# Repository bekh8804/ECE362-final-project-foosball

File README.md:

# ECE362-final-project-foosball
Patchy Was here
Gideon Was here

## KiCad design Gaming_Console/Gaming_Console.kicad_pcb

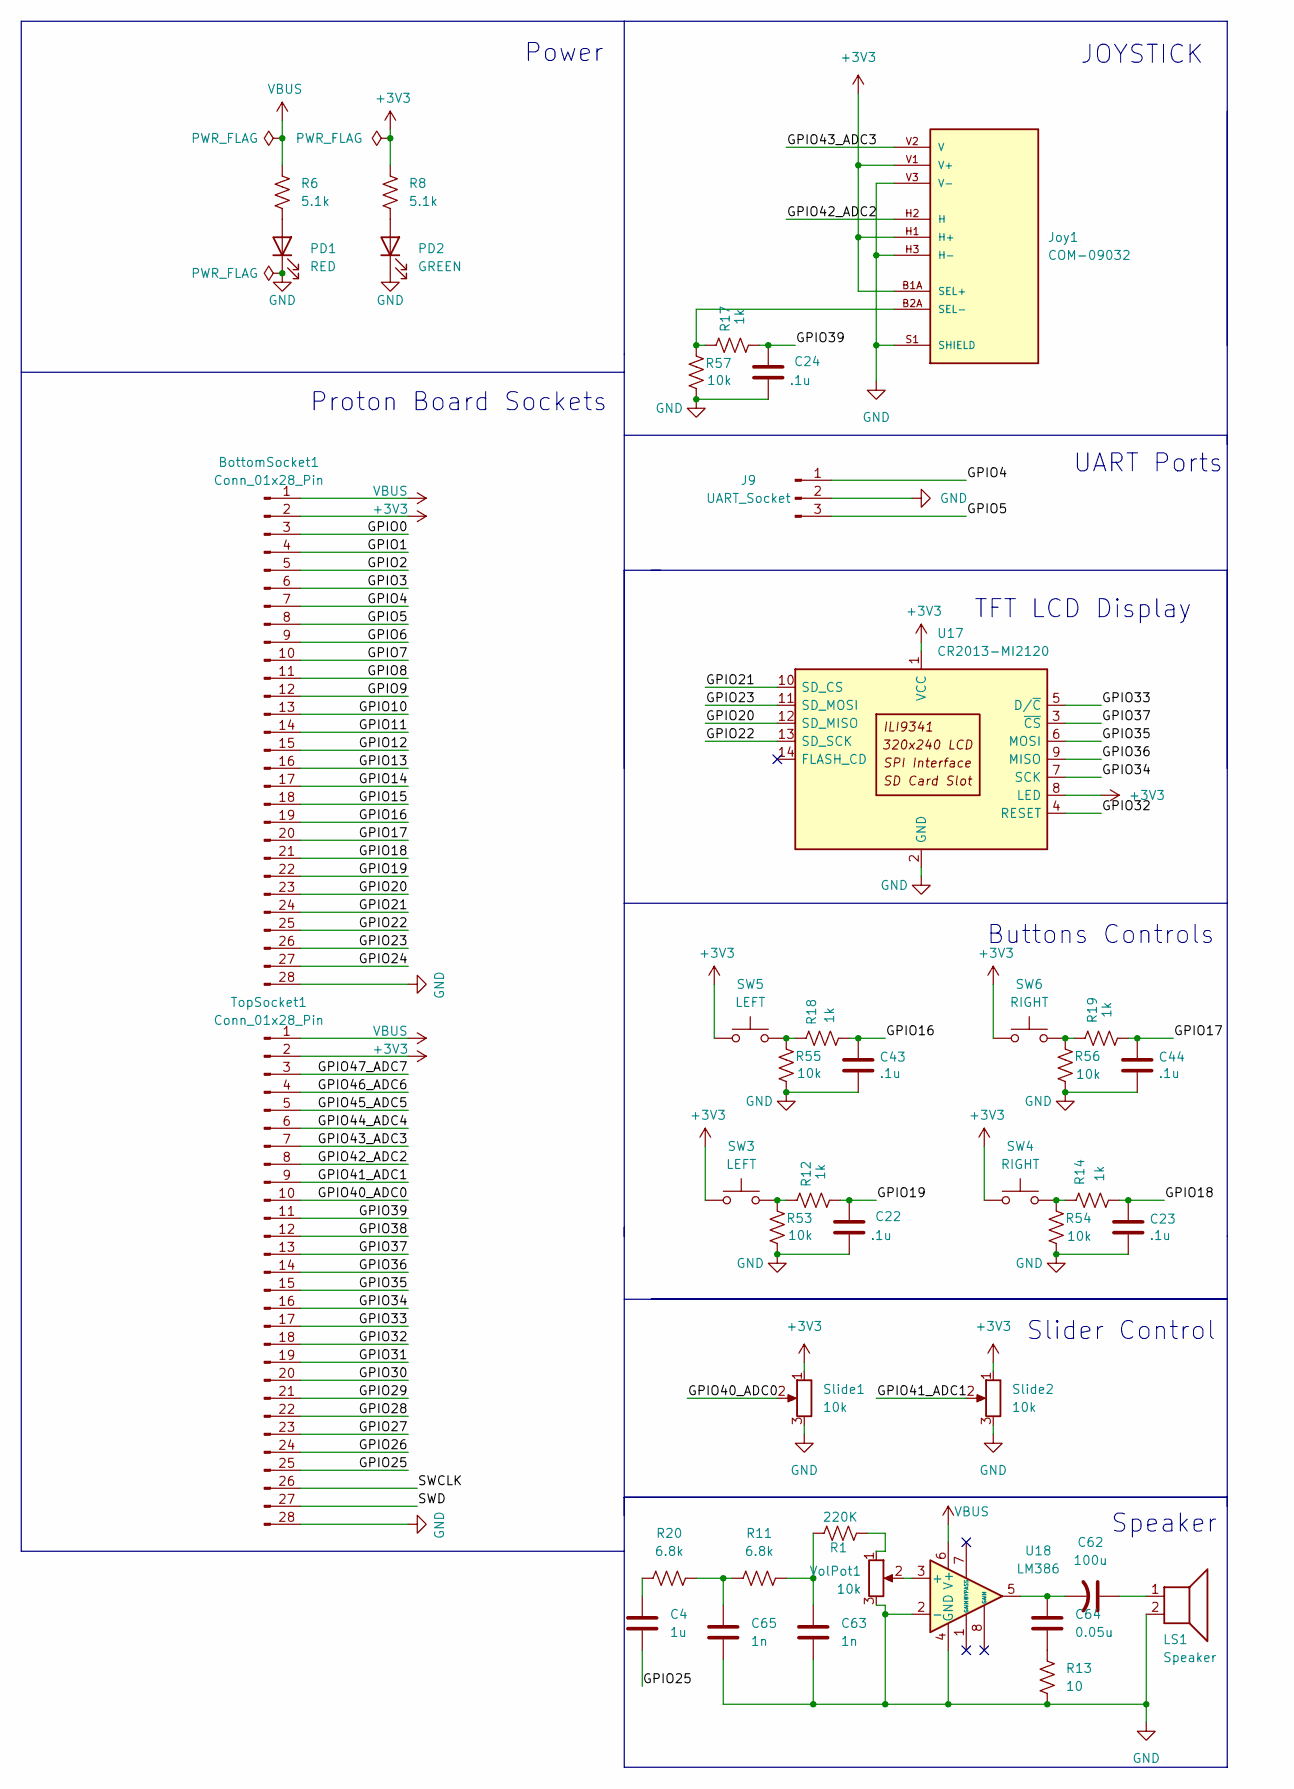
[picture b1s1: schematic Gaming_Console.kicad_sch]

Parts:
BottomSocket1: Conn_01x28_Pin; PinSocket_1x28_P2.54mm_Vertical
C4: 1u; C_0805_2012Metric
C22, C23, C24, C43, C44: .1u; C_0805_2012Metric
C62: 100u; C_0805_2012Metric
C63, C65: 1n; C_0805_2012Metric
C64: 0.05u; C_0805_2012Metric
J9: UART_Socket; JST_PH_S3B-PH-K_1x03_P2.00mm_Horizontal; MPN PRPC003SACN-RC
Joy1: COM-09032; XDCR_COM-09032; MPN COM-09032
LS1: Speaker; Speaker_CUI_CMR-1206S-67
PD1: RED; LED_0805_2012Metric; MPN LS R976-NR-1-0-20-R18
PD2: GREEN; LED_0805_2012Metric; MPN LG R971-KN-1-0-20-R18
R1: 220K; R_0805_2012Metric
R6, R8: 5.1k; R_0805_2012Metric; MPN RK73H1ETTP5101F
R11, R20: 6.8k; R_0805_2012Metric
R12, R14, R17, R18, R19: 1k; R_0805_2012Metric; MPN RC0402JR-071KL
R13: 10; R_0805_2012Metric
R53, R54, R55, R56, R57: 10k; R_0805_2012Metric
SW3, SW5: LEFT; SW_SPST_PTS647_Sx38; MPN PTS647SM38SMTR2 LFS
SW4, SW6: RIGHT; SW_SPST_PTS647_Sx38; MPN PTS647SM38SMTR2 LFS
Slide1, Slide2: 10k; Potentiometer_Bourns_PTA2043_Single_Slide
TopSocket1: Conn_01x28_Pin; PinSocket_1x28_P2.54mm_Vertical
U17: CR2013-MI2120
U18: LM386; DIP-8_W7.62mm
VolPot1: 10k; Potentiometer_Alps_RK09K_Single_Vertical

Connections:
+3V3: BottomSocket1.2, Joy1.B1A (SEL+), Joy1.H1 (H+), Joy1.V1 (V+), R8.1, SW3.1, SW4.1, SW5.1, SW6.1, Slide1.1, Slide2.1, TopSocket1.2, U17.1 (VCC), U17.8 (LED)
/GPIO0: BottomSocket1.3
/GPIO1: BottomSocket1.4
/GPIO2: BottomSocket1.5
/GPIO3: BottomSocket1.6
/GPIO4: BottomSocket1.7, J9.1
/GPIO5: BottomSocket1.8, J9.3
/GPIO6: BottomSocket1.9
/GPIO7: BottomSocket1.10
/GPIO8: BottomSocket1.11
/GPIO9: BottomSocket1.12
/GPIO10: BottomSocket1.13
/GPIO11: BottomSocket1.14
/GPIO12: BottomSocket1.15
/GPIO13: BottomSocket1.16
/GPIO14: BottomSocket1.17
/GPIO15: BottomSocket1.18
/GPIO16: BottomSocket1.19, C43.1, R18.2
/GPIO17: BottomSocket1.20, C44.1, R19.2
/GPIO18: BottomSocket1.21, C23.1, R14.2
/GPIO19: BottomSocket1.22, C22.1, R12.2
/GPIO20: BottomSocket1.23, U17.12 (SD_MISO)
/GPIO21: BottomSocket1.24, U17.10 (SD_CS)
/GPIO22: BottomSocket1.25, U17.13 (SD_SCK)
/GPIO23: BottomSocket1.26, U17.11 (SD_MOSI)
/GPIO24: BottomSocket1.27
/GPIO25: C4.2, TopSocket1.25
/GPIO26: TopSocket1.24
/GPIO27: TopSocket1.23
/GPIO28: TopSocket1.22
/GPIO29: TopSocket1.21
/GPIO30: TopSocket1.20
/GPIO31: TopSocket1.19
/GPIO32: TopSocket1.18, U17.4 (RESET)
/GPIO33: TopSocket1.17, U17.5 (D/~C)
/GPIO34: TopSocket1.16, U17.7 (SCK)
/GPIO35: TopSocket1.15, U17.6 (MOSI)
/GPIO36: TopSocket1.14, U17.9 (MISO)
/GPIO37: TopSocket1.13, U17.3 (~CS)
/GPIO38: TopSocket1.12
/GPIO39: C24.1, R17.2, TopSocket1.11
/GPIO40_ADC0: Slide1.2, TopSocket1.10
/GPIO41_ADC1: Slide2.2, TopSocket1.9
/GPIO42_ADC2: Joy1.H2 (H), TopSocket1.8
/GPIO43_ADC3: Joy1.V2 (V), TopSocket1.7
/GPIO44_ADC4: TopSocket1.6
/GPIO45_ADC5: TopSocket1.5
/GPIO46_ADC6: TopSocket1.4
/GPIO47_ADC7: TopSocket1.3
/SWCLK: TopSocket1.26
/SWD: TopSocket1.27
GND: BottomSocket1.28, C22.2, C23.2, C24.2, C43.2, C44.2, C63.2, C65.2, J9.2, Joy1.H3 (H-), Joy1.S1 (SHIELD), Joy1.S2 (SHIELD), Joy1.S3 (SHIELD), Joy1.S4 (SHIELD), Joy1.V3 (V-), LS1.2, PD1.1 (K), PD2.1 (K), R13.2, R53.1, R54.1, R55.1, R56.1, R57.1, Slide1.3, Slide2.3, TopSocket1.28, U17.2 (GND), U18.2 (-), U18.4 (GND), VolPot1.3
unnamed: C4.1, R20.2
unnamed: C62.1, LS1.1
unnamed: C62.2, C64.1, U18.5
unnamed: C63.1, R1.1, R11.1
unnamed: C64.2, R13.1
unnamed: C65.1, R11.2, R20.1
unnamed: Joy1.B2A (SEL-), R17.1, R57.2
unnamed: PD1.2 (A), R6.2
unnamed: PD2.2 (A), R8.2
unnamed: R1.2, VolPot1.1
unnamed: R12.1, R53.2, SW3.2
unnamed: R14.1, R54.2, SW4.2
unnamed: R18.1, R55.2, SW5.2
unnamed: R19.1, R56.2, SW6.2
unnamed: U18.3 (+), VolPot1.2
VBUS: BottomSocket1.1, R6.1, TopSocket1.1, U18.6 (V+)

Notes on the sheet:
TFT LCD Display
Power
Slider Control
UART Ports
JOYSTICK
Buttons Controls
Proton Board Sockets
Speaker

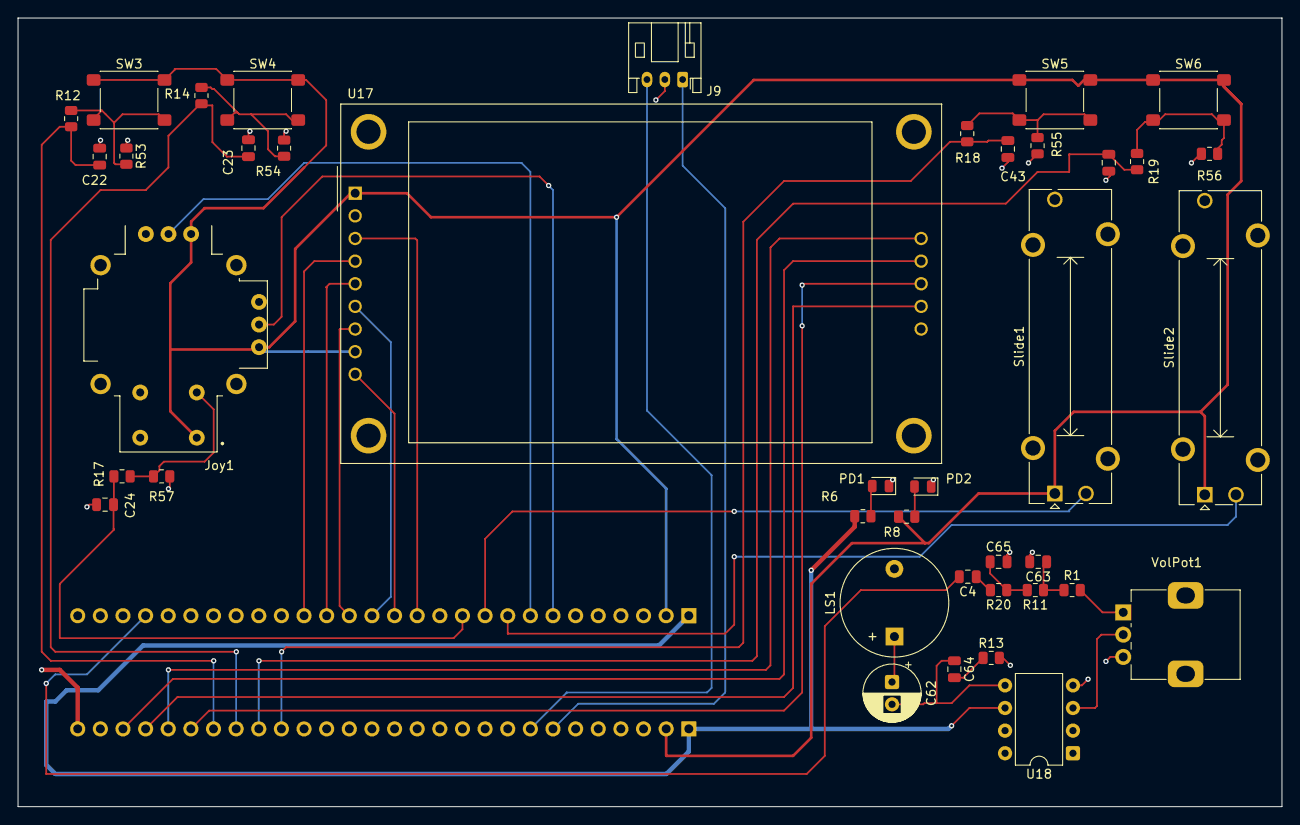
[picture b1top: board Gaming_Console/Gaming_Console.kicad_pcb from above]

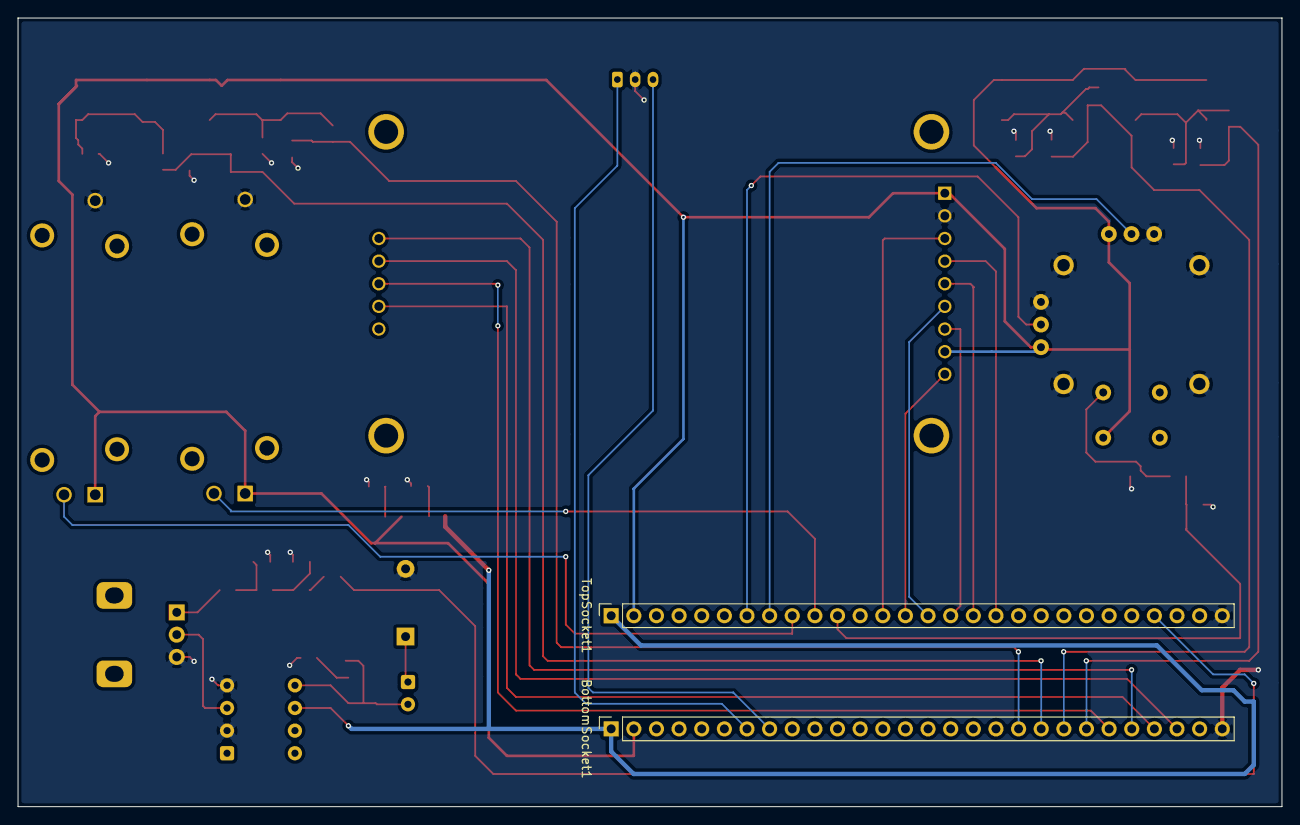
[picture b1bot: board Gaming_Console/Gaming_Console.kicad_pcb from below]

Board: 2 copper layers, 141.8 x 88.5 mm, 42 parts (2 on the bottom side), 40 nets.

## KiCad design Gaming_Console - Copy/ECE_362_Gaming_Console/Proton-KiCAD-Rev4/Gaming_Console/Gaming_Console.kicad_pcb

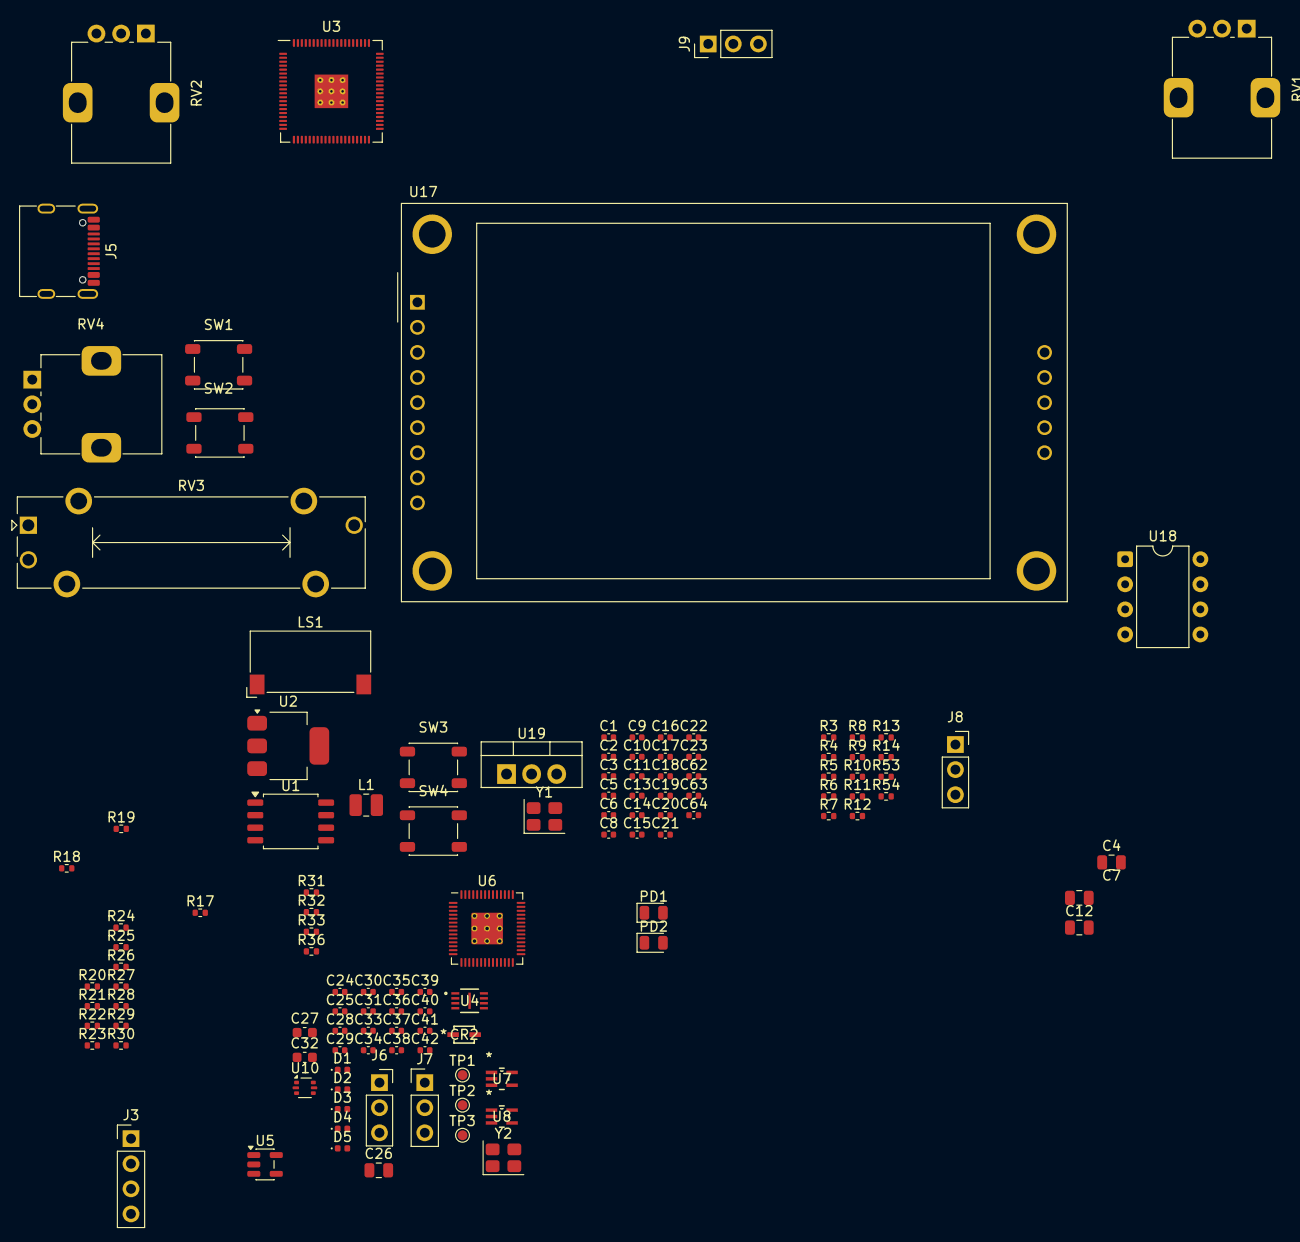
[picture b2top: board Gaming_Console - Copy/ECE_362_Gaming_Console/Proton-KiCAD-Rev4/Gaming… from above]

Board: 2 copper layers, 118 parts (0 on the bottom side), 96 nets, no tracks yet.

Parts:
C1, C2, C24, C25: 15p; C_0402_1005Metric
C3, C8, C11, C13, C14, C15, C16, C17, C18, C19, C20, C21, C28, C29, C30, C33, C35, C36, C37, C38, C39, C40, C41, C42: 100n; C_0402_1005Metric
C4, C7, C12, C26: 10u; C_0805_2012Metric
C5, C6, C9, C10: 4.7u; C_0402_1005Metric
C22, C23: DNF; C_0402_1005Metric
C27, C32: 10u; C_0603_1608Metric
C31, C34: 1u; C_0402_1005Metric
C62: 100u; C_0402_1005Metric
C63: 1n; C_0402_1005Metric
C64: 0.05u; C_0402_1005Metric
CR2: BAT60JFILM; CR_60JFILM_STM
D1: RED; D_0402_1005Metric
D2, D4: GREEN; D_0402_1005Metric
D3, D5: YELLOW; D_0402_1005Metric
J3: Conn_01x04_Pin; PinHeader_1x04_P2.54mm_Vertical
J5: USB_C_Receptacle_USB2.0_14P; USB_C_Receptacle_G-Switch_GT-USB-7010ASV
J6, J8: Conn_01x03_Socket; PinSocket_1x03_P2.54mm_Vertical
J7: UART-PINS; PinHeader_1x03_P2.54mm_Vertical
J9: UART_Socket; PinHeader_1x03_P2.54mm_Vertical
L1: 3.3u; L_1008_2520Metric
LS1: Speaker; Speaker_CUI_CMR-1206S-67
PD1: RED; LED_0805_2012Metric
PD2: GREEN; LED_0805_2012Metric
R3, R4, R7, R12, R14, R17, R20, R36: 1k; R_0402_1005Metric
R5: 33; R_0402_1005Metric
R6, R8, R18, R19: 5.1k; R_0402_1005Metric
R9, R10, R21, R22: 27; R_0402_1005Metric
R11: 10k; R_0402_1005Metric
R13: 10; R_0402_1005Metric
R23, R31, R33: 470; R_0402_1005Metric
R24, R25, R26, R27, R28, R29: 100; R_0402_1005Metric
R30, R32: 2k; R_0402_1005Metric
R53, R54: DNF; R_0402_1005Metric
RV1: Pot1; Potentiometer_Alps_RK09K_Single_Vertical
RV2: Pot2; Potentiometer_Alps_RK09K_Single_Vertical
RV3: Pot3; Potentiometer_Bourns_PTA2043_Single_Slide
RV4: VolPot; Potentiometer_Alps_RK09K_Single_Vertical
SW1: BOOTSEL; SW_SPST_PTS647_Sx38
SW2: RESET; SW_SPST_PTS647_Sx38
SW3: LEFT; SW_SPST_PTS647_Sx38
SW4: RIGHT; SW_SPST_PTS647_Sx38
TP1: RESET; TestPoint_Pad_D1.0mm
TP2: SWCLK; TestPoint_Pad_D1.0mm
TP3: SWD; TestPoint_Pad_D1.0mm
U1: W25Q128JVS; SOIC-8_5.3x5.3mm_P1.27mm
U2: NCP1117-3.3_SOT223; SOT-223-3_TabPin2
U3: RP2350_80QFN; RP2350-QFN-80-1EP_10x10_P0.4mm_EP3.4x3.4mm_ThermalVias
U4: W25Q16JVUXIQ TR; USON-8_UX_2x3x0p6_WIN
U5: AP2112K-3.3; SOT-23-5
U6: RP2040; RP2040-QFN-56
U7, U8: SN74AUP1T17DCKR; DCK5
U10: USBLC6-2P6; SOT-666
U17: CR2013-MI2120
U18: LM386; DIP-8_W7.62mm
U19: LM7805_TO220; TO-220-3_Vertical
Y1, Y2: ABM8-272-T3; Crystal_SMD_3225-4Pin_3.2x2.5mm

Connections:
+1V1: C6.1, C8.1, C10.1, C11.1, L1.1, U3.10 (DVDD), U3.32 (DVDD), U3.51 (DVDD), U3.65 (VREG_FB)
+3V3: C3.1, C5.1, C12.1, C13.1, C14.1, C15.1, C16.1, C17.1, C18.1, C19.1, C20.1, C21.1, R5.1, R8.1, R12.1, R14.1, RV1.1, RV2.1, RV3.1, U1.8 (VCC), U3.5 (IOVDD), U3.15 (IOVDD), U3.24 (IOVDD), U3.29 (IOVDD), U3.41 (IOVDD), U3.50 (IOVDD), U3.59 (ADC_AVDD), U3.60 (IOVDD), U3.64 (VREG_VIN), U3.68 (USB_OTP_VDD), U3.69 (QSPI_IOVDD), U3.76 (IOVDD), U17.1 (VCC), U17.8 (LED)
+P1V1: C28.1, C30.1, C31.1, U6.23 (DVDD), U6.45 (VREG_VOUT), U6.50 (DVDD)
+P3V3: C27.1, C29.1, C32.1, C33.1, C34.1, C35.1, C36.1, C37.1, C38.1, C39.1, C40.1, C41.1, C42.1, R36.1, U4.8 (VCC), U5.5 (VOUT), U6.1 (IOVDD), U6.10 (IOVDD), U6.22 (IOVDD), U6.33 (IOVDD), U6.42 (IOVDD), U6.43 (ADC_AVDD), U6.44 (VREG_IN), U6.48 (USB_VDD), U6.49 (IOVDD), U7.5 (VCC), U8.5 (VCC)
/3.3V: C7.1, U2.2 (VO)
/DebugProbe/GPIO2: R23.1, U6.4 (GPIO2)
/DebugProbe/GPIO4: R24.1, U6.6 (GPIO4)
/DebugProbe/GPIO5: U6.7 (GPIO5), U7.4 (Y)
/DebugProbe/GPIO6: R25.1, U6.8 (GPIO6)
/DebugProbe/GPIO7: R30.1, U6.9 (GPIO7)
/DebugProbe/GPIO8: R31.1, U6.11 (GPIO8)
/DebugProbe/GPIO12: R27.1, U6.15 (GPIO12)
/DebugProbe/GPIO13: U6.16 (GPIO13), U8.4 (Y)
/DebugProbe/GPIO14: R28.1, U6.17 (GPIO14)
/DebugProbe/GPIO15: R32.1, U6.18 (GPIO15)
/DebugProbe/GPIO16: R33.1, U6.27 (GPIO16)
/DebugProbe/QSPI_SCLK: U4.6 (CLK), U6.52 (QSPI_SCLK)
/DebugProbe/QSPI_SD0: U4.5 (DI(IO0)), U6.53 (QSPI_SD0)
/DebugProbe/QSPI_SD1: U4.2 (DO(IO1)), U6.55 (QSPI_SD1)
/DebugProbe/QSPI_SD2: U4.3 (/WP(IO2)), U6.54 (QSPI_SD2)
/DebugProbe/QSPI_SD3: U4.7 (/HOLDOR/RESET(IO3)), U6.51 (QSPI_SD3)
/DebugProbe/QSPI_SS: R17.1, U4.1 (/CS), U6.56 (QSPI_SS)
/DebugProbe/RESET: R36.2, TP1.1 (1_1), U6.26 (RUN)
/DebugProbe/USB_D+: R21.1, U10.4 (I/O2)
/DebugProbe/USB_D-: R22.1, U10.6 (I/O1)
/DebugProbe/XIN: C24.1, U6.20 (XIN), Y2.1
/DebugProbe/XOUT: R20.1, U6.21 (XOUT)
/DebugProbe/~USB_BOOT: J3.1, R17.2
/FLASH_SS: R7.1, U1.1 (~CS), U3.75 (QSPI_SS)
/GPIO4: J9.1, U3.1 (GPIO4)
/GPIO5: J9.3, U3.2 (GPIO5)
/GPIO18: C23.1, R54.2, SW4.2, U3.18 (GPIO18)
/GPIO19: C22.1, R53.2, SW3.2, U3.19 (GPIO19)
/GPIO20: U3.20 (GPIO20), U17.12 (SD_MISO)
/GPIO21: U3.21 (GPIO21), U17.10 (SD_CS)
/GPIO22: U3.22 (GPIO22), U17.13 (SD_SCK)
/GPIO23: U3.23 (GPIO23), U17.11 (SD_MOSI)
/GPIO25: RV4.1, U3.26 (GPIO25)
/GPIO34: U3.43 (GPIO34), U17.7 (SCK)
/GPIO35: U3.44 (GPIO35), U17.6 (MOSI)
/GPIO36: U3.45 (GPIO36), U17.9 (MISO)
/GPIO37: U3.46 (GPIO37), U17.3 (~CS)
/GPIO40_ADC0: RV1.2, U3.49 (GPIO40_ADC0)
/GPIO41_ADC1: RV2.2, U3.52 (GPIO41_ADC1)
/GPIO42_ADC2: RV3.2, U3.53 (GPIO42_ADC2)
/QSPI_SCLK: U1.6 (CLK), U3.71 (QSPI_SCLK)
/QSPI_SD0: U1.5 (DI(IO0)), U3.72 (QSPI_SD0)
/QSPI_SD1: U1.2 (DO(IO1)), U3.74 (QSPI_SD1)
/QSPI_SD2: U1.3 (IO2), U3.73 (QSPI_SD2)
/QSPI_SD3: U1.7 (IO3), U3.70 (QSPI_SD3)
/RUN: SW2.2, U3.35 (RUN), U17.4 (RESET)
/SWCLK: J8.1, U3.33 (SWCLK)
/SWD: J8.3, U3.34 (SWD)
/VREG_AVDD: C9.1, R5.2, U3.61 (VREG_AVDD)
/VREG_LX: L1.2, U3.63 (VREG_LX)
/XIN: C1.1, U3.30 (XIN), Y1.1
/XOUT: R3.1, U3.31 (XOUT)
/~USB_BOOT: R7.2, SW1.2
GND: C1.2, C2.2, C3.2, C4.2, C5.2, C6.2, C7.2, C8.2, C9.2, C10.2, C11.2, C12.2, C13.2, C14.2, C15.2, C16.2, C17.2, C18.2, C19.2, C20.2, C21.2, C22.2, C23.2, C63.2, J8.2, J9.2, LS1.2, PD1.1 (K), PD2.1 (K), R4.2, R13.2, R53.1, R54.1, RV1.3, RV2.3, RV3.3, RV4.3, SW1.1, U1.4 (GND), U2.1 (GND), U3.62 (VREG_PGND), U3.81 (GND), U17.2 (GND), U18.2 (-), U18.4 (GND), U19.2 (GND), Y1.2, Y1.4
unnamed: C2.1, R3.2, Y1.3
unnamed: C25.1, R20.2, Y2.3
unnamed: C62.1, LS1.1
unnamed: C62.2, C64.1, U18.5
unnamed: C64.2, R13.1
unnamed: CR2.2, J5.A4 (VBUS), J5.A9 (VBUS), J5.B4 (VBUS), J5.B9 (VBUS)
unnamed: D1.2 (A), R23.2
unnamed: D2.2 (A), R30.2
unnamed: D3.2 (A), R31.2
unnamed: D4.2 (A), R32.2
unnamed: D5.2 (A), R33.2
unnamed: J5.A5 (CC1), R18.1
unnamed: J5.B5 (CC2), R19.1
unnamed: J5.A6 (D+), J5.B6 (D+), U10.3 (I/O2)
unnamed: J5.A7 (D-), J5.B7 (D-), U10.1 (I/O1)
unnamed: J7.1, R24.2
unnamed: J7.3, R25.2, R26.2
unnamed: PD1.2 (A), R6.2
unnamed: PD2.2 (A), R8.2
unnamed: R4.1, SW2.1
unnamed: R11.2, RV4.2
unnamed: R12.2, SW3.1
unnamed: R14.2, SW4.1
unnamed: R10.2, U3.66 (USB_DM)
unnamed: R9.2, U3.67 (USB_DP)
unnamed: TP2.1 (1_1), U6.24 (SWCLK)
unnamed: TP3.1 (1_1), U6.25 (SWD)
unnamed: R22.2, U6.46 (USB_DM)
unnamed: R21.2, U6.47 (USB_DP)
unnamed: R26.1, U7.2 (A)
unnamed: R29.1, U8.2 (A)
unnamed: C63.1, R11.1, U18.3 (+)
PGND: C24.2, C25.2, C26.2, C27.2, C28.2, C29.2, C30.2, C31.2, C32.2, C33.2, C34.2, C35.2, C36.2, C37.2, C38.2, C39.2, C40.2, C41.2, C42.2, D1.1 (K), D2.1 (K), D3.1 (K), D4.1 (K), D5.1 (K), J3.3, J5.A1 (GND), J5.A12 (GND), J5.B1 (GND), J5.B12 (GND), J6.2, J7.2, R18.2, R19.2, U4.4 (GND), U5.2 (GND), U6.19 (TESTEN), U6.57 (GND), U7.3 (GND), U8.3 (GND), U10.2 (GND), Y2.2, Y2.4
PSWCLK: J3.2, J6.1, R27.2
PSWD: J3.4, J6.3, R28.2, R29.2
P_VBUS: C26.1, CR2.1, U5.1 (VIN), U5.3 (EN), U10.5 (VBUS)
VBUS: C4.1, R6.1, U2.3 (VI), U19.3 (VO)
